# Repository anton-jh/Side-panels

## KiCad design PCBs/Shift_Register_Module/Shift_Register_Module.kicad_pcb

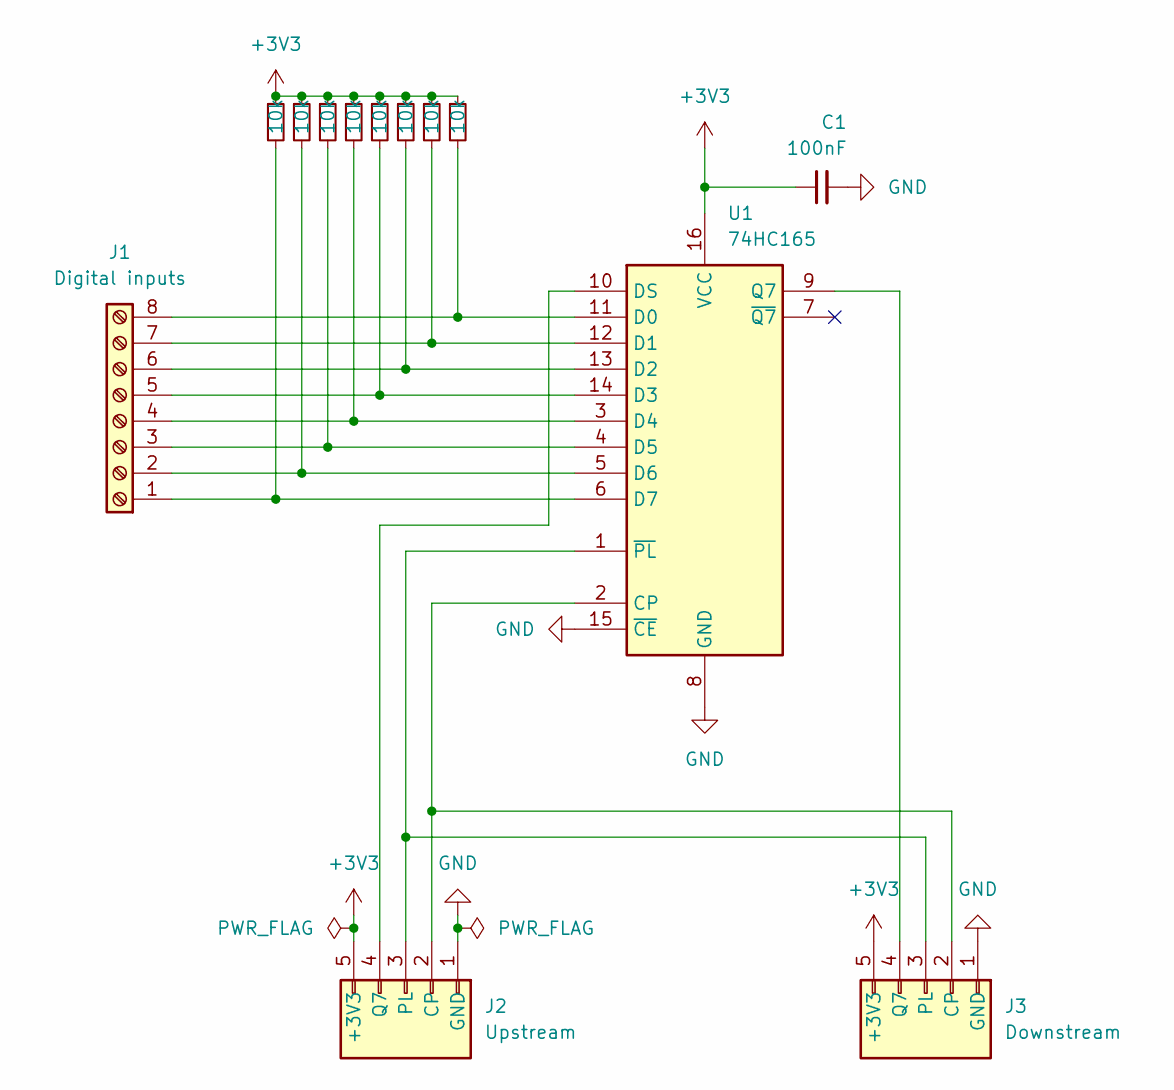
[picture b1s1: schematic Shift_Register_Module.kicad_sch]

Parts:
C1: 100nF; C_Disc_D5.0mm_W2.5mm_P2.50mm
J1: Digital inputs; TerminalBlock_Phoenix_MPT-0,5-8-2.54_1x08_P2.54mm_Horizontal
J2: Upstream; PinSocket_1x05_P2.54mm_Horizontal
J3: Downstream; PinHeader_1x05_P2.54mm_Horizontal
R1, R2, R3, R4, R5, R6, R7, R8: 10k; R_Axial_DIN0204_L3.6mm_D1.6mm_P1.90mm_Vertical
U1: 74HC165; DIP-16_W7.62mm_Socket

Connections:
+3V3: C1.1, J2.5 (+3V3), J3.5 (+3V3), R1.1, R2.1, R3.1, R4.1, R5.1, R6.1, R7.1, R8.1, U1.16 (VCC)
GND: C1.2, J2.1 (GND), J3.1 (GND), U1.8 (GND), U1.15 (~CE)
unnamed: J1.1, R1.2, U1.6 (D7)
unnamed: J1.2, R2.2, U1.5 (D6)
unnamed: J1.3, R3.2, U1.4 (D5)
unnamed: J1.4, R4.2, U1.3 (D4)
unnamed: J1.5, R5.2, U1.14 (D3)
unnamed: J1.6, R6.2, U1.13 (D2)
unnamed: J1.7, R7.2, U1.12 (D1)
unnamed: J1.8, R8.2, U1.11 (D0)
unnamed: J2.2 (CP), J3.2 (CP), U1.2 (CP)
unnamed: J2.4 (SER), U1.10 (DS)
unnamed: J2.3 (/PL), J3.3 (/PL), U1.1 (~PL)
unnamed: J3.4 (SER), U1.9 (Q7)

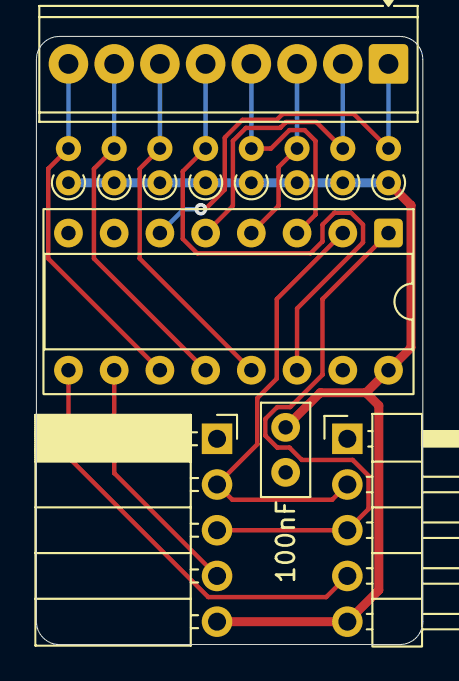
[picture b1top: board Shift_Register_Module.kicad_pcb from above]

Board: 2 copper layers, 21.5 x 33.8 mm, 13 parts (0 on the bottom side), 14 nets.

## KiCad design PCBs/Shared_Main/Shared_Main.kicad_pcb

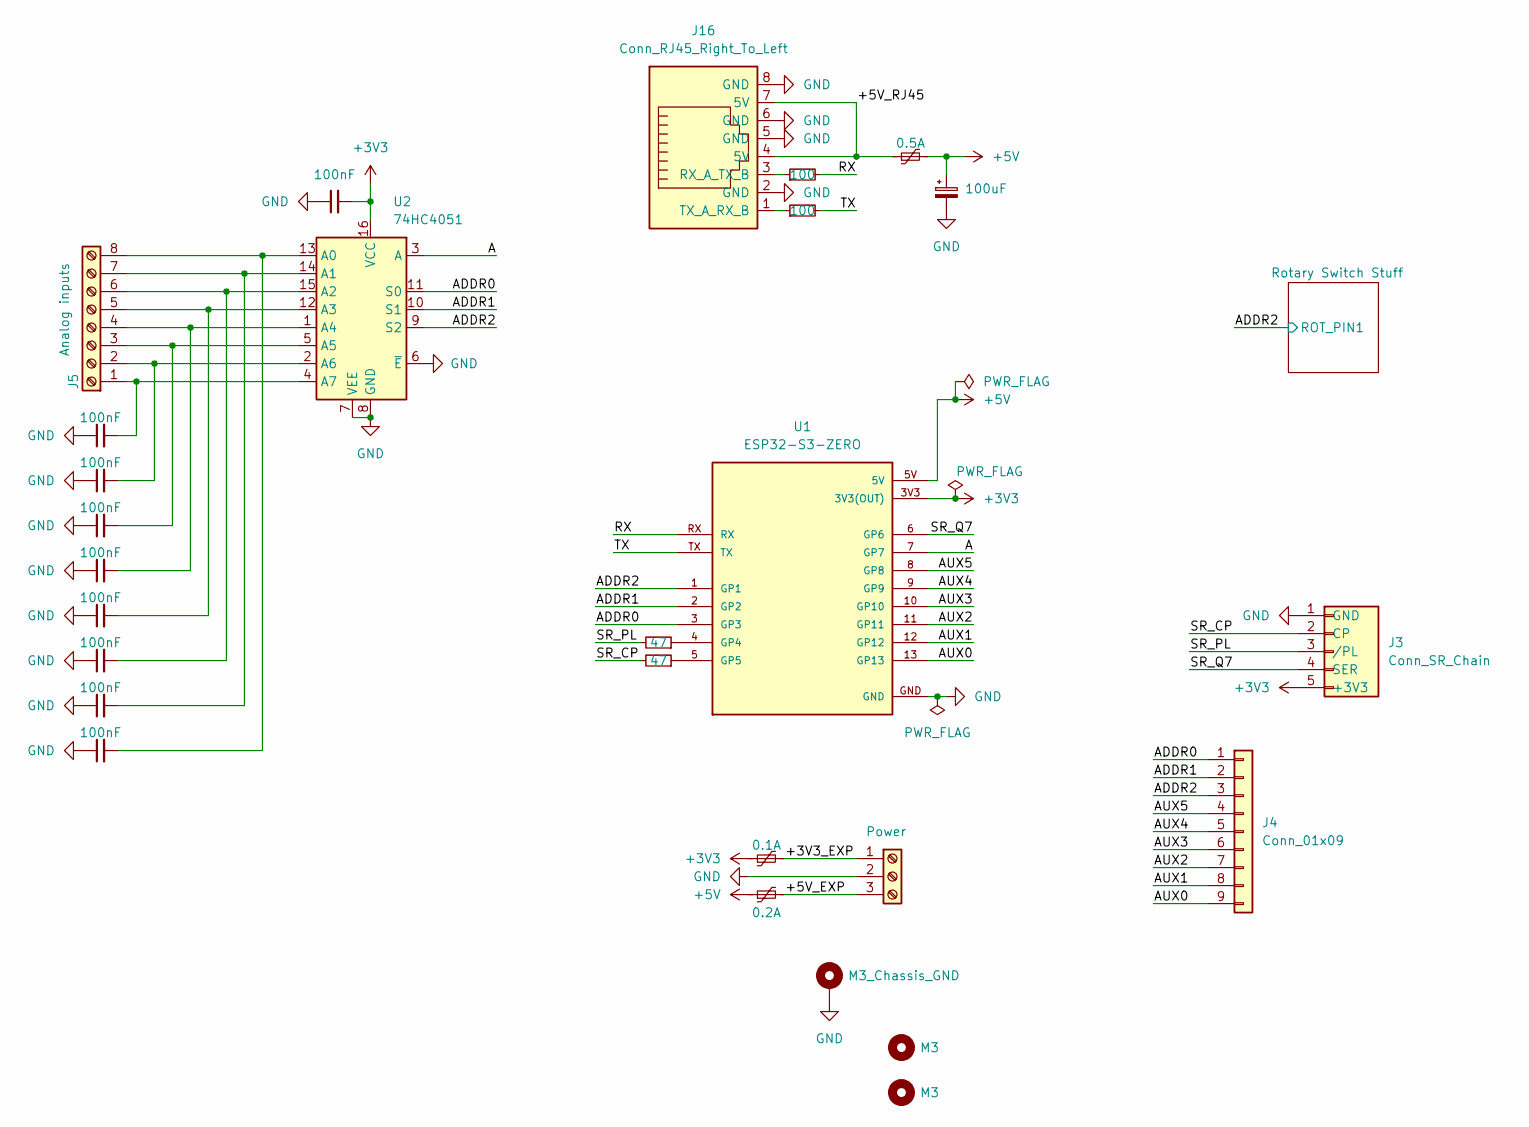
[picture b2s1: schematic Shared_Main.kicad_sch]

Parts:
C1, C12, C13, C14, C15, C16, C17, C18, C19: 100nF; C_Disc_D5.0mm_W2.5mm_P2.50mm
C3: 100uF; CP_Radial_D5.0mm_P2.00mm
F1: 0.5A; Fuse_Bourns_MF-RHT050
F2: 0.1A; Fuse_Bourns_MF-RHT050
F3: 0.2A; Fuse_Bourns_MF-RHT050
H1: M3_Chassis_GND; MountingHole_3.2mm_M3_DIN965_Pad_TopOnly
H2, H3: M3; MountingHole_3.2mm_M3
J1: Power; TerminalBlock_Phoenix_MKDS-1,5-3_1x03_P5.00mm_Horizontal
J3: Conn_SR_Chain; PinSocket_1x05_P2.54mm_Horizontal
J4: Conn_01x09; PinHeader_1x09_P2.54mm_Vertical
J5: Analog inputs; TerminalBlock_Phoenix_MPT-0,5-8-2.54_1x08_P2.54mm_Horizontal
J16: Conn_RJ45_Right_To_Left; RJ45_Amphenol_54602-x08_Horizontal
R2, R3: 100; R_Axial_DIN0207_L6.3mm_D2.5mm_P7.62mm_Horizontal
R9, R10: 47; R_Axial_DIN0207_L6.3mm_D2.5mm_P7.62mm_Horizontal
U1: ESP32-S3-ZERO; MODULE_ESP32-S3-ZERO; PARTREV NA
U2: 74HC4051; DIP-16_W7.62mm_Socket

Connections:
+3V3: C1.2, F2.1, J3.5 (+3V3), U1.3V3 (3V3(OUT)), U2.16 (VCC)
+5V: C3.1, F1.2, F3.1, U1.5V
/+3V3_EXP: F2.2, J1.1
/+5V_EXP: F3.2, J1.3
/+5V_RJ45: F1.1, J16.4 (5V), J16.7 (5V)
/A: U1.7 (GP7), U2.3 (A)
/ADDR0: J4.1, U1.3 (GP3), U2.11 (S0)
/ADDR1: J4.2, U1.2 (GP2), U2.10 (S1)
/ADDR2: J4.3, U1.1 (GP1), U2.9 (S2); also elsewhere on the board
/AUX0: J4.9, U1.13 (GP13)
/AUX1: J4.8, U1.12 (GP12)
/AUX2: J4.7, U1.11 (GP11)
/AUX3: J4.6, U1.10 (GP10)
/AUX4: J4.5, U1.9 (GP9)
/AUX5: J4.4, U1.8 (GP8)
/RX: R2.2, U1.RX
/SR_CP: J3.2 (CP), R10.2
/SR_PL: J3.3 (/PL), R9.2
/SR_Q7: J3.4 (SER), U1.6 (GP6)
/TX: R3.2, U1.TX
GND: C1.1, C3.2, C12.1, C13.1, C14.1, C15.1, C16.1, C17.1, C18.1, C19.1, H1.1 (1_1), J1.2, J3.1 (GND), J16.2 (GND), J16.5 (GND), J16.6 (GND), J16.8 (GND), U1.GND, U2.6 (~E), U2.7 (VEE), U2.8 (GND); also elsewhere on the board
unnamed: C12.2, J5.1, U2.4 (A7)
unnamed: C13.2, J5.2, U2.2 (A6)
unnamed: C14.2, J5.3, U2.5 (A5)
unnamed: C15.2, J5.4, U2.1 (A4)
unnamed: C16.2, J5.5, U2.12 (A3)
unnamed: C17.2, J5.6, U2.15 (A2)
unnamed: C18.2, J5.7, U2.14 (A1)
unnamed: C19.2, J5.8, U2.13 (A0)
unnamed: J16.3 (RX_A_TX_B), R2.1
unnamed: J16.1 (TX_A_RX_B), R3.1
unnamed: R9.1, U1.4 (GP4)
unnamed: R10.1, U1.5 (GP5)

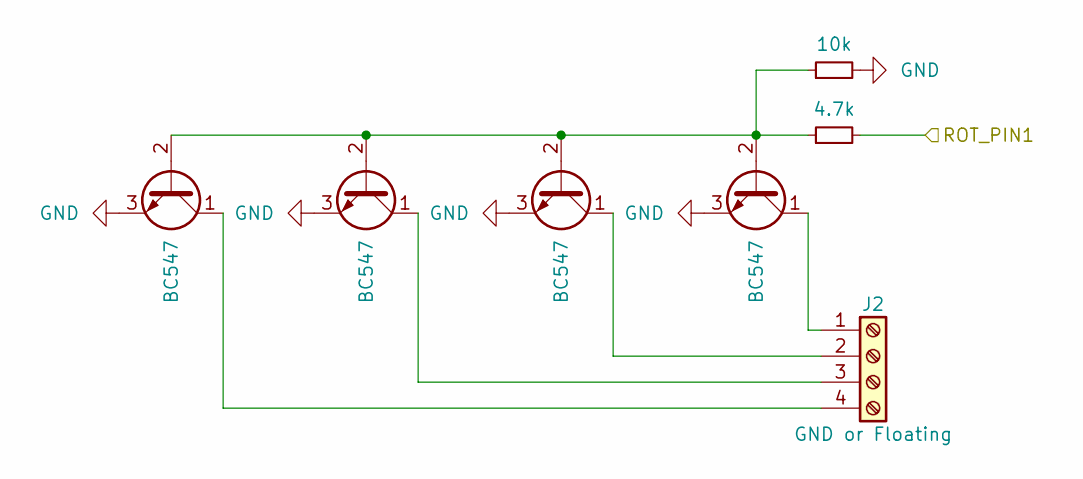
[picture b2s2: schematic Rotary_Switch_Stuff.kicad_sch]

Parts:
J2: GND or Floating; TerminalBlock_Phoenix_MPT-0,5-4-2.54_1x04_P2.54mm_Horizontal
Q1, Q2, Q3, Q4: BC547; TO-92_Inline_Wide
R1: 4.7k; R_Axial_DIN0207_L6.3mm_D2.5mm_P7.62mm_Horizontal
R7: 10k; R_Axial_DIN0207_L6.3mm_D2.5mm_P7.62mm_Horizontal

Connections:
/ADDR2: R1.2; also elsewhere on the board
GND: Q1.3 (E), Q2.3 (E), Q3.3 (E), Q4.3 (E), R7.2; also elsewhere on the board
unnamed: J2.1, Q4.1 (C)
unnamed: J2.2, Q3.1 (C)
unnamed: J2.3, Q2.1 (C)
unnamed: J2.4, Q1.1 (C)
unnamed: Q1.2 (B), Q2.2 (B), Q3.2 (B), Q4.2 (B), R1.1, R7.1

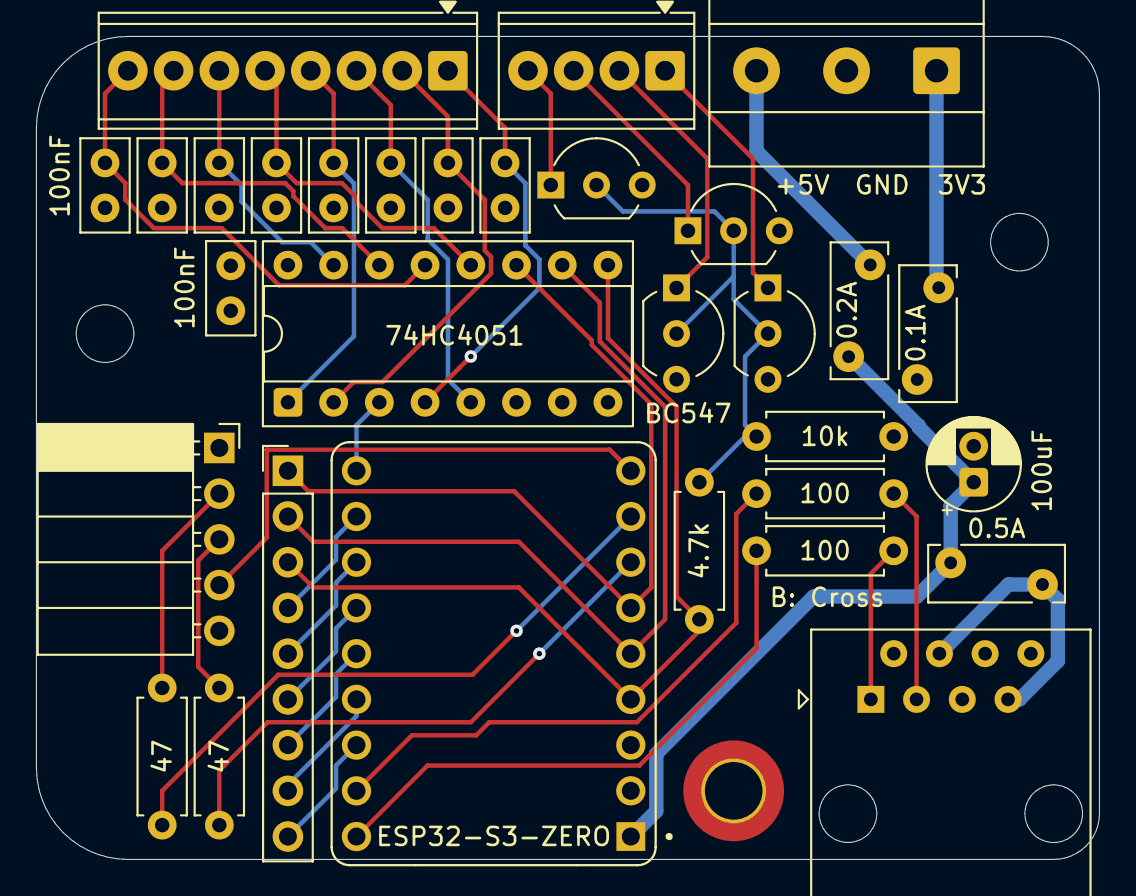
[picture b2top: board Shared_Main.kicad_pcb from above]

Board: 4 copper layers, 59.1 x 45.7 mm, 34 parts (0 on the bottom side), 38 nets.

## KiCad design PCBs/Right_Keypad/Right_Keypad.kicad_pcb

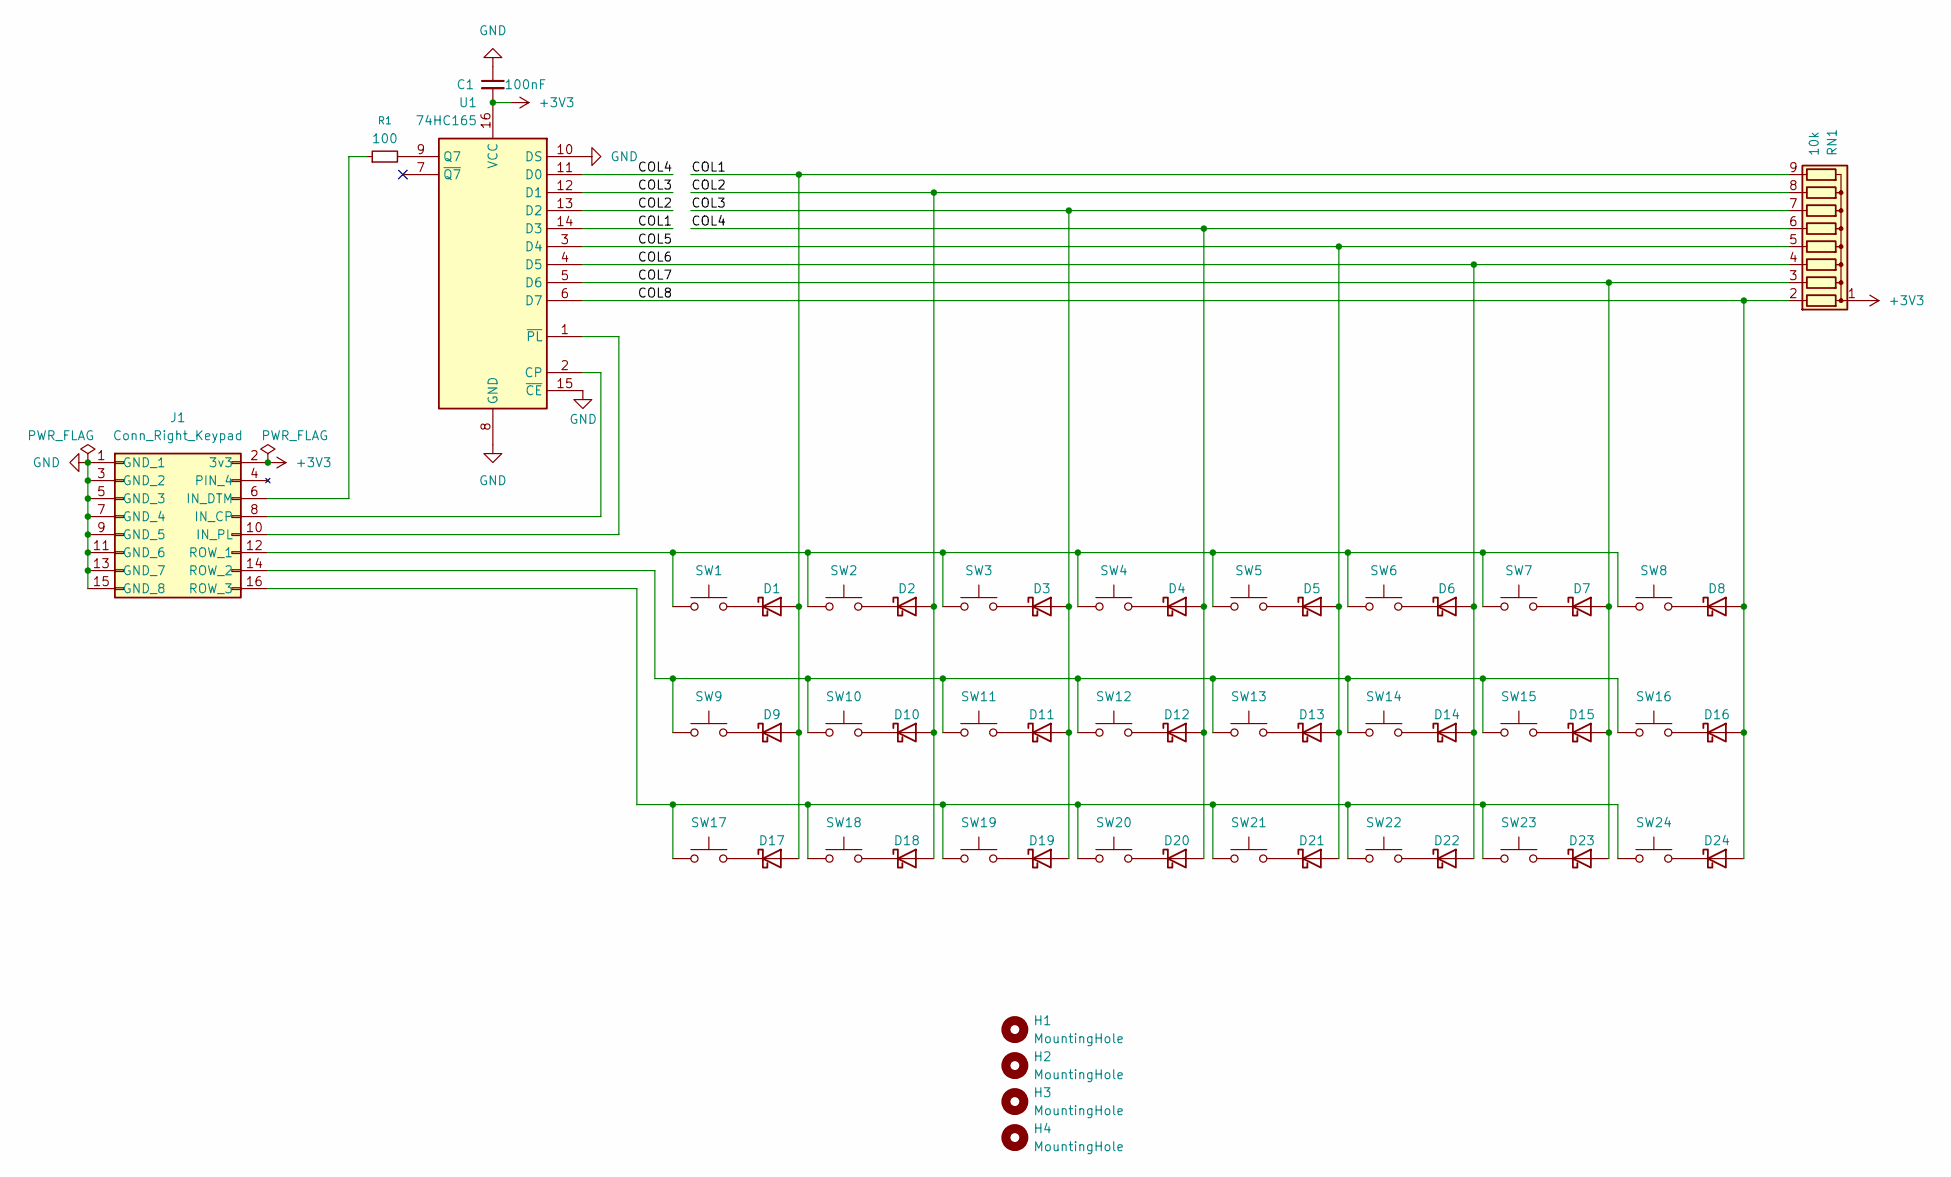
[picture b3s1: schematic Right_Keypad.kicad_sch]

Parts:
C1: 100nF; C_Disc_D5.0mm_W2.5mm_P2.50mm
D1, D2, D3, D4, D5, D6, D7, D8, D9, D10, D11, D12, D13, D14, D15, D16, D17, D18, D19, D20, D21, D22, D23, D24: SD103AWS; D_SOD-323_HandSoldering
H1, H2, H3, H4: MountingHole; MountingHole_3.2mm_M3
J1: Conn_Right_Keypad; IDC-Header_2x08_P2.54mm_Vertical
R1: 100; R_Axial_DIN0207_L6.3mm_D2.5mm_P7.62mm_Horizontal
RN1: 10k; R_Array_SIP9
SW1, SW2, SW3, SW4, SW5, SW6, SW7, SW8, SW9, SW10, SW11, SW12, SW13, SW14, SW15, SW16, SW17, SW18, SW19, SW20, SW21, SW22, SW23, SW24: SW_Push; SW_PUSH-12mm_Grid
U1: 74HC165; DIP-16_W7.62mm

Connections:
+3V3: C1.2, J1.2 (3v3), RN1.1 (common), U1.16 (VCC)
/COL1: D1.2 (A), D9.2 (A), D17.2 (A), RN1.9 (R8), U1.14 (D3)
/COL2: D2.2 (A), D10.2 (A), D18.2 (A), RN1.8 (R7), U1.13 (D2)
/COL3: D3.2 (A), D11.2 (A), D19.2 (A), RN1.7 (R6), U1.12 (D1)
/COL4: D4.2 (A), D12.2 (A), D20.2 (A), RN1.6 (R5), U1.11 (D0)
/COL5: D5.2 (A), D13.2 (A), D21.2 (A), RN1.5 (R4), U1.3 (D4)
/COL6: D6.2 (A), D14.2 (A), D22.2 (A), RN1.4 (R3), U1.4 (D5)
/COL7: D7.2 (A), D15.2 (A), D23.2 (A), RN1.3 (R2), U1.5 (D6)
/COL8: D8.2 (A), D16.2 (A), D24.2 (A), RN1.2 (R1), U1.6 (D7)
GND: C1.1, J1.1 (GND_1), J1.3 (GND_2), J1.5 (GND_3), J1.7 (GND_4), J1.9 (GND_5), J1.11 (GND_6), J1.13 (GND_7), J1.15 (GND_8), U1.8 (GND), U1.10 (DS), U1.15 (~CE)
unnamed: D1.1 (K), SW1.2
unnamed: D2.1 (K), SW2.2
unnamed: D3.1 (K), SW3.2
unnamed: D4.1 (K), SW4.2
unnamed: D5.1 (K), SW5.2
unnamed: D6.1 (K), SW6.2
unnamed: D7.1 (K), SW7.2
unnamed: D8.1 (K), SW8.2
unnamed: D9.1 (K), SW9.2
unnamed: D10.1 (K), SW10.2
unnamed: D11.1 (K), SW11.2
unnamed: D12.1 (K), SW12.2
unnamed: D13.1 (K), SW13.2
unnamed: D14.1 (K), SW14.2
unnamed: D15.1 (K), SW15.2
unnamed: D16.1 (K), SW16.2
unnamed: D17.1 (K), SW17.2
unnamed: D18.1 (K), SW18.2
unnamed: D19.1 (K), SW19.2
unnamed: D20.1 (K), SW20.2
unnamed: D21.1 (K), SW21.2
unnamed: D22.1 (K), SW22.2
unnamed: D23.1 (K), SW23.2
unnamed: D24.1 (K), SW24.2
unnamed: J1.8 (IN_CP), U1.2 (CP)
unnamed: J1.6 (IN_DTM), R1.1
unnamed: J1.10 (IN_PL), U1.1 (~PL)
unnamed: J1.12 (ROW_1), SW1.1, SW2.1, SW3.1, SW4.1, SW5.1, SW6.1, SW7.1, SW8.1
unnamed: J1.14 (ROW_2), SW9.1, SW10.1, SW11.1, SW12.1, SW13.1, SW14.1, SW15.1, SW16.1
unnamed: J1.16 (ROW_3), SW17.1, SW18.1, SW19.1, SW20.1, SW21.1, SW22.1, SW23.1, SW24.1
unnamed: R1.2, U1.9 (Q7)

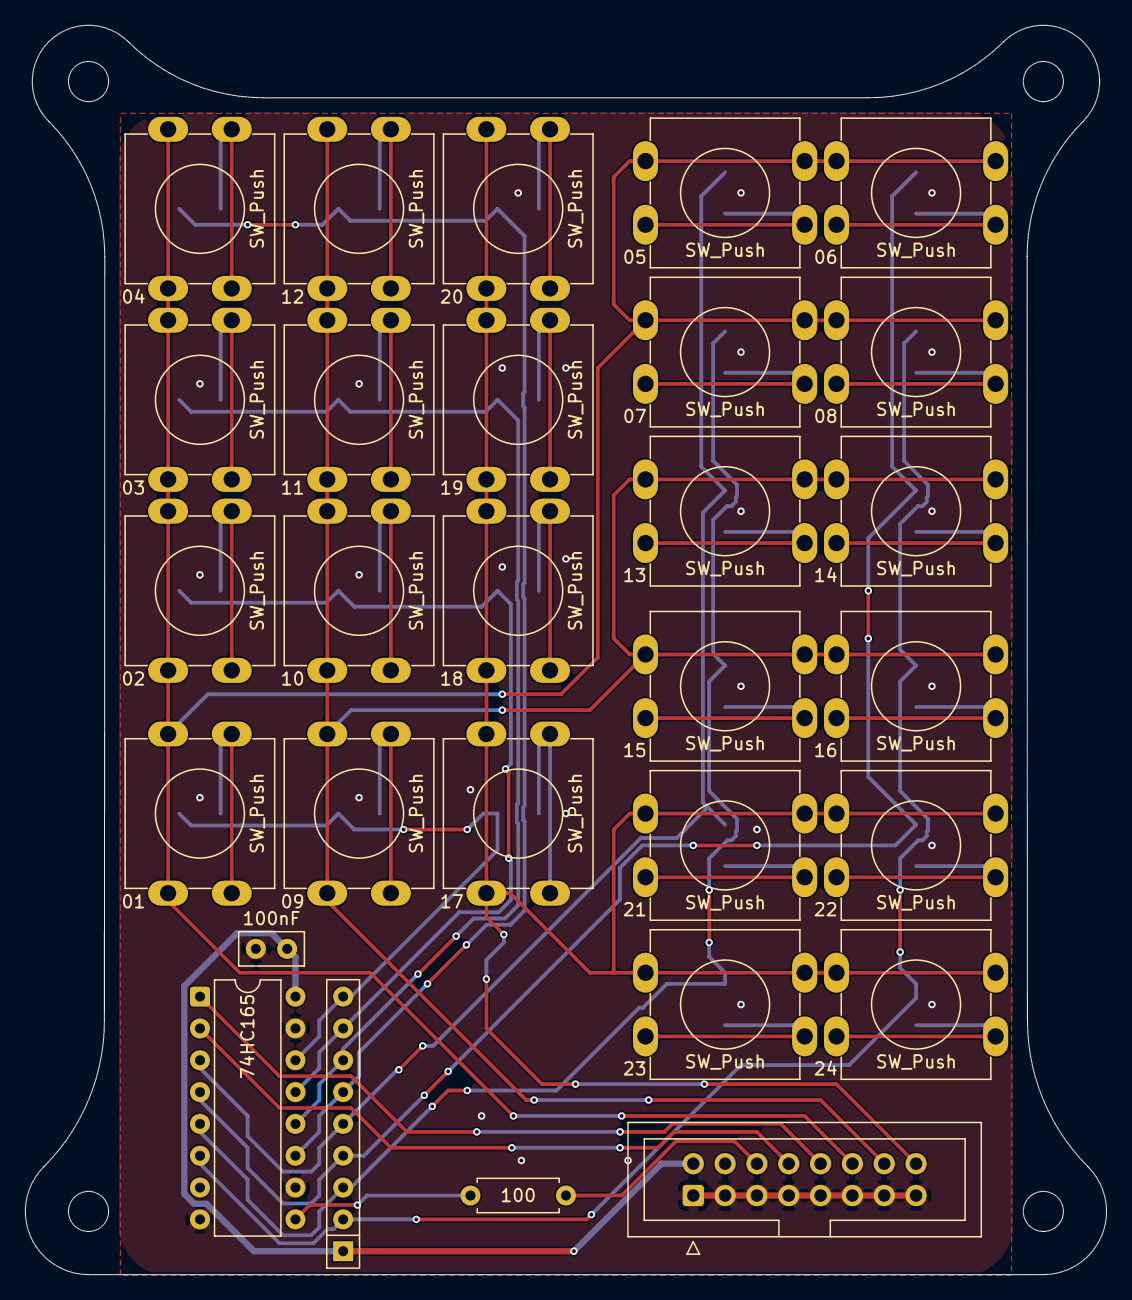
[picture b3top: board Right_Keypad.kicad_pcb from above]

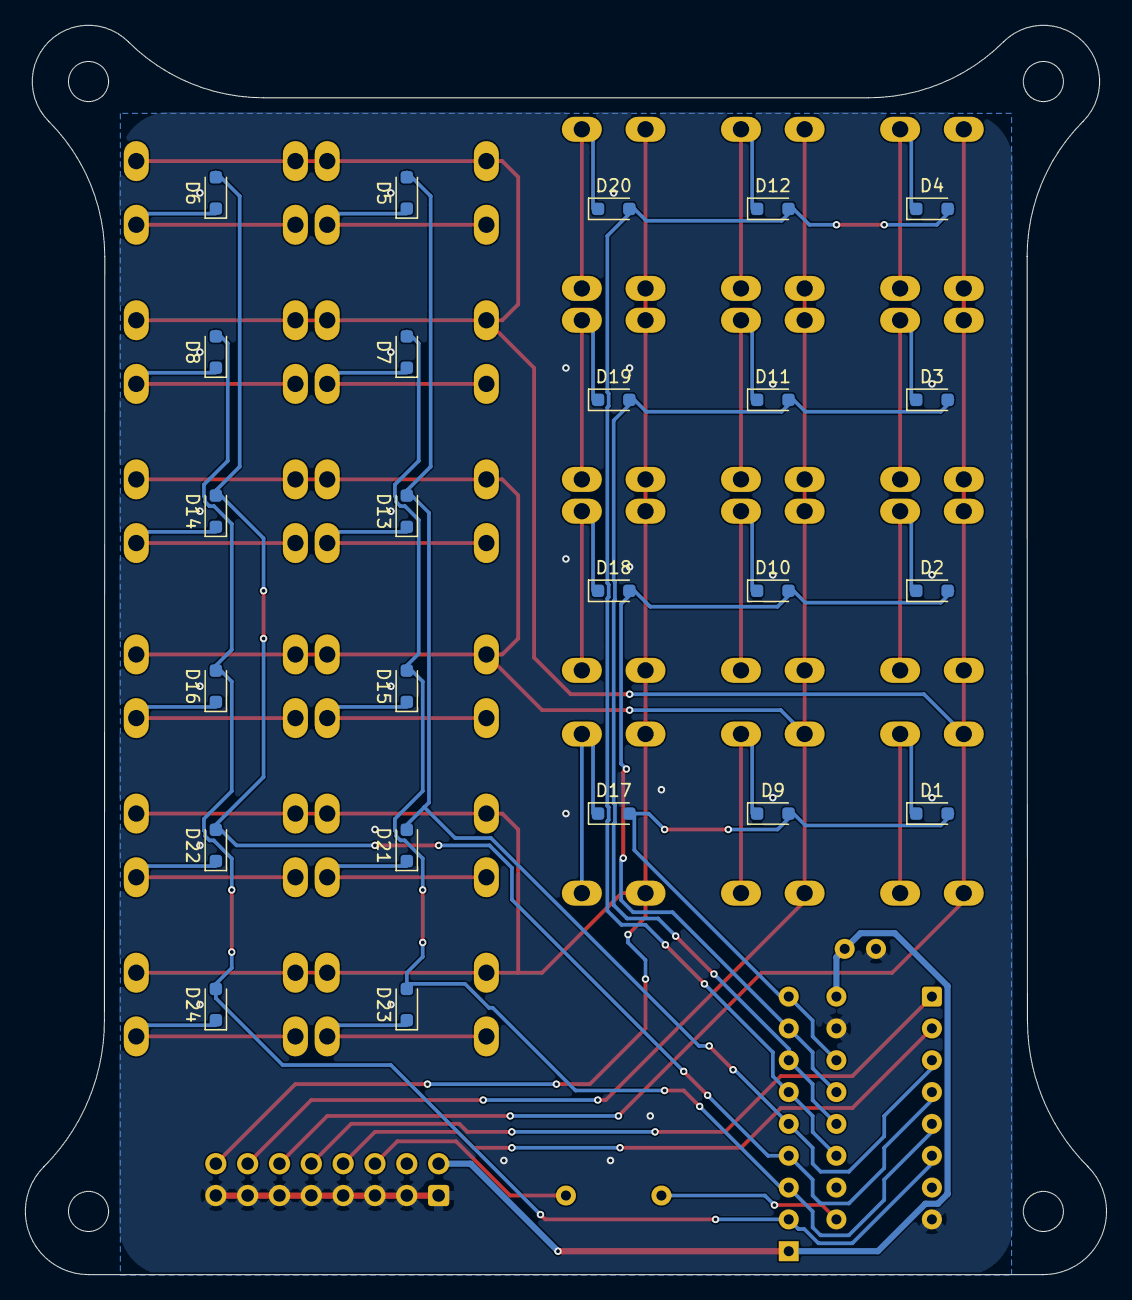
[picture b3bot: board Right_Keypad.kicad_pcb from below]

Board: 2 copper layers, 86.3 x 99.7 mm, 57 parts (24 on the bottom side), 41 nets.

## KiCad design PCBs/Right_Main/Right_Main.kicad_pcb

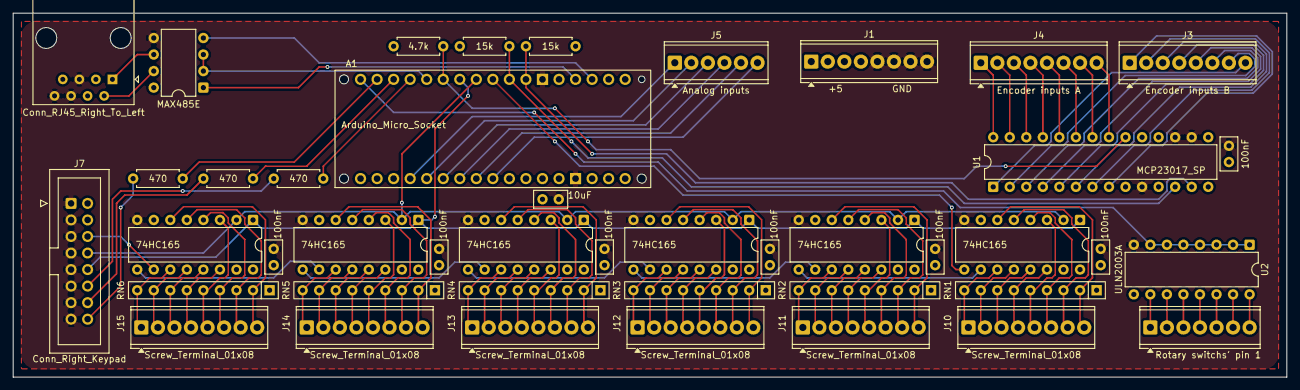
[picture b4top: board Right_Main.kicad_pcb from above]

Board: 4 copper layers, 195.6 x 55.9 mm, 43 parts (0 on the bottom side), 103 nets.

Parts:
A1: Arduino_Micro_Socket
C1, C4, C5, C6, C7, C8, C9: 100nF; C_Disc_D5.0mm_W2.5mm_P2.50mm
C2: 10uF; C_Disc_D5.0mm_W2.5mm_P2.50mm
J1: +5V and GND; TerminalBlock_Phoenix_MPT-0,5-8-2.54_1x08_P2.54mm_Horizontal
J3: Encoder inputs B; TerminalBlock_Phoenix_MPT-0,5-8-2.54_1x08_P2.54mm_Horizontal
J4: Encoder inputs A; TerminalBlock_Phoenix_MPT-0,5-8-2.54_1x08_P2.54mm_Horizontal
J5: Analog inputs; TerminalBlock_Phoenix_MPT-0,5-6-2.54_1x06_P2.54mm_Horizontal
J7: Conn_Right_Keypad; IDC-Header_2x08_P2.54mm_Vertical
J8: Rotary switchs' pin 1; TerminalBlock_Phoenix_MPT-0,5-7-2.54_1x07_P2.54mm_Horizontal
J10, J11, J12, J13, J14, J15: Screw_Terminal_01x08; TerminalBlock_Phoenix_MPT-0,5-8-2.54_1x08_P2.54mm_Horizontal
J16: Conn_RJ45_Right_To_Left; RJ45_Amphenol_54602-x08_Horizontal
R1, R2: 15k; R_Axial_DIN0207_L6.3mm_D2.5mm_P7.62mm_Horizontal
R3: 4.7k; R_Axial_DIN0207_L6.3mm_D2.5mm_P7.62mm_Horizontal
R4, R5, R6: 470; R_Axial_DIN0207_L6.3mm_D2.5mm_P7.62mm_Horizontal
RN1, RN2, RN3, RN4, RN5, RN6: R_Network08; R_Array_SIP9
U1: MCP23017_SP; DIP-28_W7.62mm
U2: ULN2003A; DIP-16_W7.62mm
U4, U5, U6, U7, U8, U9: 74HC165; DIP-16_W7.62mm
U10: MAX485E; DIP-8_W7.62mm

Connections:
+5V: A1.5V, C1.1, C2.2, C4.2, C5.2, C6.2, C7.2, C8.2, C9.2, J1.1, J1.2, J1.3, J1.4, J7.2 (5V), J16.3 (+), J16.4 (+), J16.7 (+), R1.2, R2.2, R3.1, RN1.1 (common), RN2.1 (common), RN3.1 (common), RN4.1 (common), RN5.1 (common), RN6.1 (common), U1.9 (VDD), U1.15 (A0), U1.18 (~RESET), U4.16 (VCC), U5.16 (VCC), U6.16 (VCC), U7.16 (VCC), U8.16 (VCC), U9.16 (VCC), U10.8 (VCC)
/Input register 1/CP: A1.D5, J7.8 (IN_CP), U4.2 (CP), U5.2 (CP), U6.2 (CP), U7.2 (CP), U8.2 (CP), U9.2 (CP)
/Input register 1/DS: U4.10 (DS), U5.9 (Q7)
/Input register 1/Q7: A1.D4, U4.9 (Q7)
/Input register 1//PL: A1.D6, J7.10 (IN_PL), U4.1 (~PL), U5.1 (~PL), U6.1 (~PL), U7.1 (~PL), U8.1 (~PL), U9.1 (~PL)
/Input register 2/DS: U5.10 (DS), U6.9 (Q7)
/Input register 3/DS: U6.10 (DS), U7.9 (Q7)
/Input register 4/DS: U7.10 (DS), U8.9 (Q7)
/Input register 5/DS: U8.10 (DS), U9.9 (Q7)
/Input register 6/DS: J7.6 (IN_DTM), U9.10 (DS)
GND: A1.GND1 (GND), A1.GND2 (GND), C1.2, C2.1, C4.1, C5.1, C6.1, C7.1, C8.1, C9.1, J1.5, J1.6, J1.7, J1.8, J7.1 (GND_1), J7.3 (GND_2), J7.5 (GND_3), J7.7 (GND_4), J7.9 (GND_5), J7.11 (GND_6), J7.13 (GND_7), J7.15 (GND_8), J16.5 (-), J16.6 (-), J16.8 (-), U1.10 (VSS), U1.16 (A1), U1.17 (A2), U2.8 (GND), U4.8 (GND), U4.15 (~CE), U5.8 (GND), U5.15 (~CE), U6.8 (GND), U6.15 (~CE), U7.8 (GND), U7.15 (~CE), U8.8 (GND), U8.15 (~CE), U9.8 (GND), U9.15 (~CE), U10.5 (GND)
unnamed: A1.D0 (D0/RX), U10.1 (RO)
unnamed: A1.D1 (D1/TX), U10.4 (DI)
unnamed: A1.D2 (D2/SDA), R2.1, U1.13 (SDA)
unnamed: A1.D3 (D3/SCL), R1.1, U1.12 (SCK)
unnamed: A1.D7 (D7_INT4), R3.2, U1.20 (INTA)
unnamed: A1.D9, R4.1
unnamed: A1.D10, R5.1
unnamed: A1.D11, R6.1
unnamed: J3.8, U1.1 (GPB0)
unnamed: J3.7, U1.2 (GPB1)
unnamed: J3.6, U1.3 (GPB2)
unnamed: J3.5, U1.4 (GPB3)
unnamed: J3.4, U1.5 (GPB4)
unnamed: J3.3, U1.6 (GPB5)
unnamed: J3.2, U1.7 (GPB6)
unnamed: J3.1, U1.8 (GPB7)
unnamed: J4.1, U1.28 (GPA7)
unnamed: J4.2, U1.27 (GPA6)
unnamed: J4.3, U1.26 (GPA5)
unnamed: J4.4, U1.25 (GPA4)
unnamed: J4.5, U1.24 (GPA3)
unnamed: J4.6, U1.23 (GPA2)
unnamed: J4.7, U1.22 (GPA1)
unnamed: J4.8, U1.21 (GPA0)
unnamed: A1.A0, J5.1
unnamed: A1.A1, J5.2
unnamed: A1.A2, J5.3
unnamed: A1.A3, J5.4
unnamed: A1.A4, J5.5
unnamed: A1.A5, J5.6
unnamed: J7.12 (ROW_1), R4.2
unnamed: J7.14 (ROW_2), R5.2
unnamed: J7.16 (ROW_3), R6.2
unnamed: J8.1, U2.10 (O7)
unnamed: J8.2, U2.11 (O6)
unnamed: J8.3, U2.12 (O5)
unnamed: J8.4, U2.13 (O4)
unnamed: J8.5, U2.14 (O3)
unnamed: J8.6, U2.15 (O2)
unnamed: J8.7, U2.16 (O1)
unnamed: J10.1, RN1.9 (R8), U4.11 (D0)
unnamed: J10.2, RN1.8 (R7), U4.12 (D1)
unnamed: J10.3, RN1.7 (R6), U4.13 (D2)
unnamed: J10.4, RN1.6 (R5), U4.14 (D3)
unnamed: J10.5, RN1.5 (R4), U4.3 (D4)
unnamed: J10.6, RN1.4 (R3), U4.4 (D5)
unnamed: J10.7, RN1.3 (R2), U4.5 (D6)
unnamed: J10.8, RN1.2 (R1), U4.6 (D7)
unnamed: J11.1, RN2.9 (R8), U5.11 (D0)
unnamed: J11.2, RN2.8 (R7), U5.12 (D1)
unnamed: J11.3, RN2.7 (R6), U5.13 (D2)
unnamed: J11.4, RN2.6 (R5), U5.14 (D3)
unnamed: J11.5, RN2.5 (R4), U5.3 (D4)
unnamed: J11.6, RN2.4 (R3), U5.4 (D5)
unnamed: J11.7, RN2.3 (R2), U5.5 (D6)
unnamed: J11.8, RN2.2 (R1), U5.6 (D7)
unnamed: J12.1, RN3.9 (R8), U6.11 (D0)
unnamed: J12.2, RN3.8 (R7), U6.12 (D1)
unnamed: J12.3, RN3.7 (R6), U6.13 (D2)
unnamed: J12.4, RN3.6 (R5), U6.14 (D3)
unnamed: J12.5, RN3.5 (R4), U6.3 (D4)
unnamed: J12.6, RN3.4 (R3), U6.4 (D5)
unnamed: J12.7, RN3.3 (R2), U6.5 (D6)
unnamed: J12.8, RN3.2 (R1), U6.6 (D7)
unnamed: J13.1, RN4.9 (R8), U7.11 (D0)
unnamed: J13.2, RN4.8 (R7), U7.12 (D1)
unnamed: J13.3, RN4.7 (R6), U7.13 (D2)
unnamed: J13.4, RN4.6 (R5), U7.14 (D3)
unnamed: J13.5, RN4.5 (R4), U7.3 (D4)
unnamed: J13.6, RN4.4 (R3), U7.4 (D5)
unnamed: J13.7, RN4.3 (R2), U7.5 (D6)
unnamed: J13.8, RN4.2 (R1), U7.6 (D7)
unnamed: J14.1, RN5.9 (R8), U8.11 (D0)
unnamed: J14.2, RN5.8 (R7), U8.12 (D1)
unnamed: J14.3, RN5.7 (R6), U8.13 (D2)
unnamed: J14.4, RN5.6 (R5), U8.14 (D3)
unnamed: J14.5, RN5.5 (R4), U8.3 (D4)
unnamed: J14.6, RN5.4 (R3), U8.4 (D5)
unnamed: J14.7, RN5.3 (R2), U8.5 (D6)
unnamed: J14.8, RN5.2 (R1), U8.6 (D7)
unnamed: J15.1, RN6.9 (R8), U9.11 (D0)
unnamed: J15.2, RN6.8 (R7), U9.12 (D1)
unnamed: J15.3, RN6.7 (R6), U9.13 (D2)
unnamed: J15.4, RN6.6 (R5), U9.14 (D3)
unnamed: J15.5, RN6.5 (R4), U9.3 (D4)
unnamed: J15.6, RN6.4 (R3), U9.4 (D5)
unnamed: J15.7, RN6.3 (R2), U9.5 (D6)
unnamed: J15.8, RN6.2 (R1), U9.6 (D7)
unnamed: J16.1 (485_A), U10.6 (A)
unnamed: J16.2 (485_B), U10.7 (B)
unnamed: A1.D12, U2.1 (I1), U2.2 (I2), U2.3 (I3), U2.4 (I4), U2.5 (I5), U2.6 (I6), U2.7 (I7)
unnamed: A1.D8, U10.2 (~RE), U10.3 (DE)

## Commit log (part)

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2025-12-23 Initial commit to combined repo
2026-01-01 before moving keypad shift regs
2026-01-03 Moved shift registers
2026-04-15 before UART+RS485
2026-06-27 UART+RS485 + KiCad 10 + keypad PCB v1
2026-06-30 ESD protection and stuff
2026-06-30 stuff
2026-06-30 finishing touches and silkscreen stuff
